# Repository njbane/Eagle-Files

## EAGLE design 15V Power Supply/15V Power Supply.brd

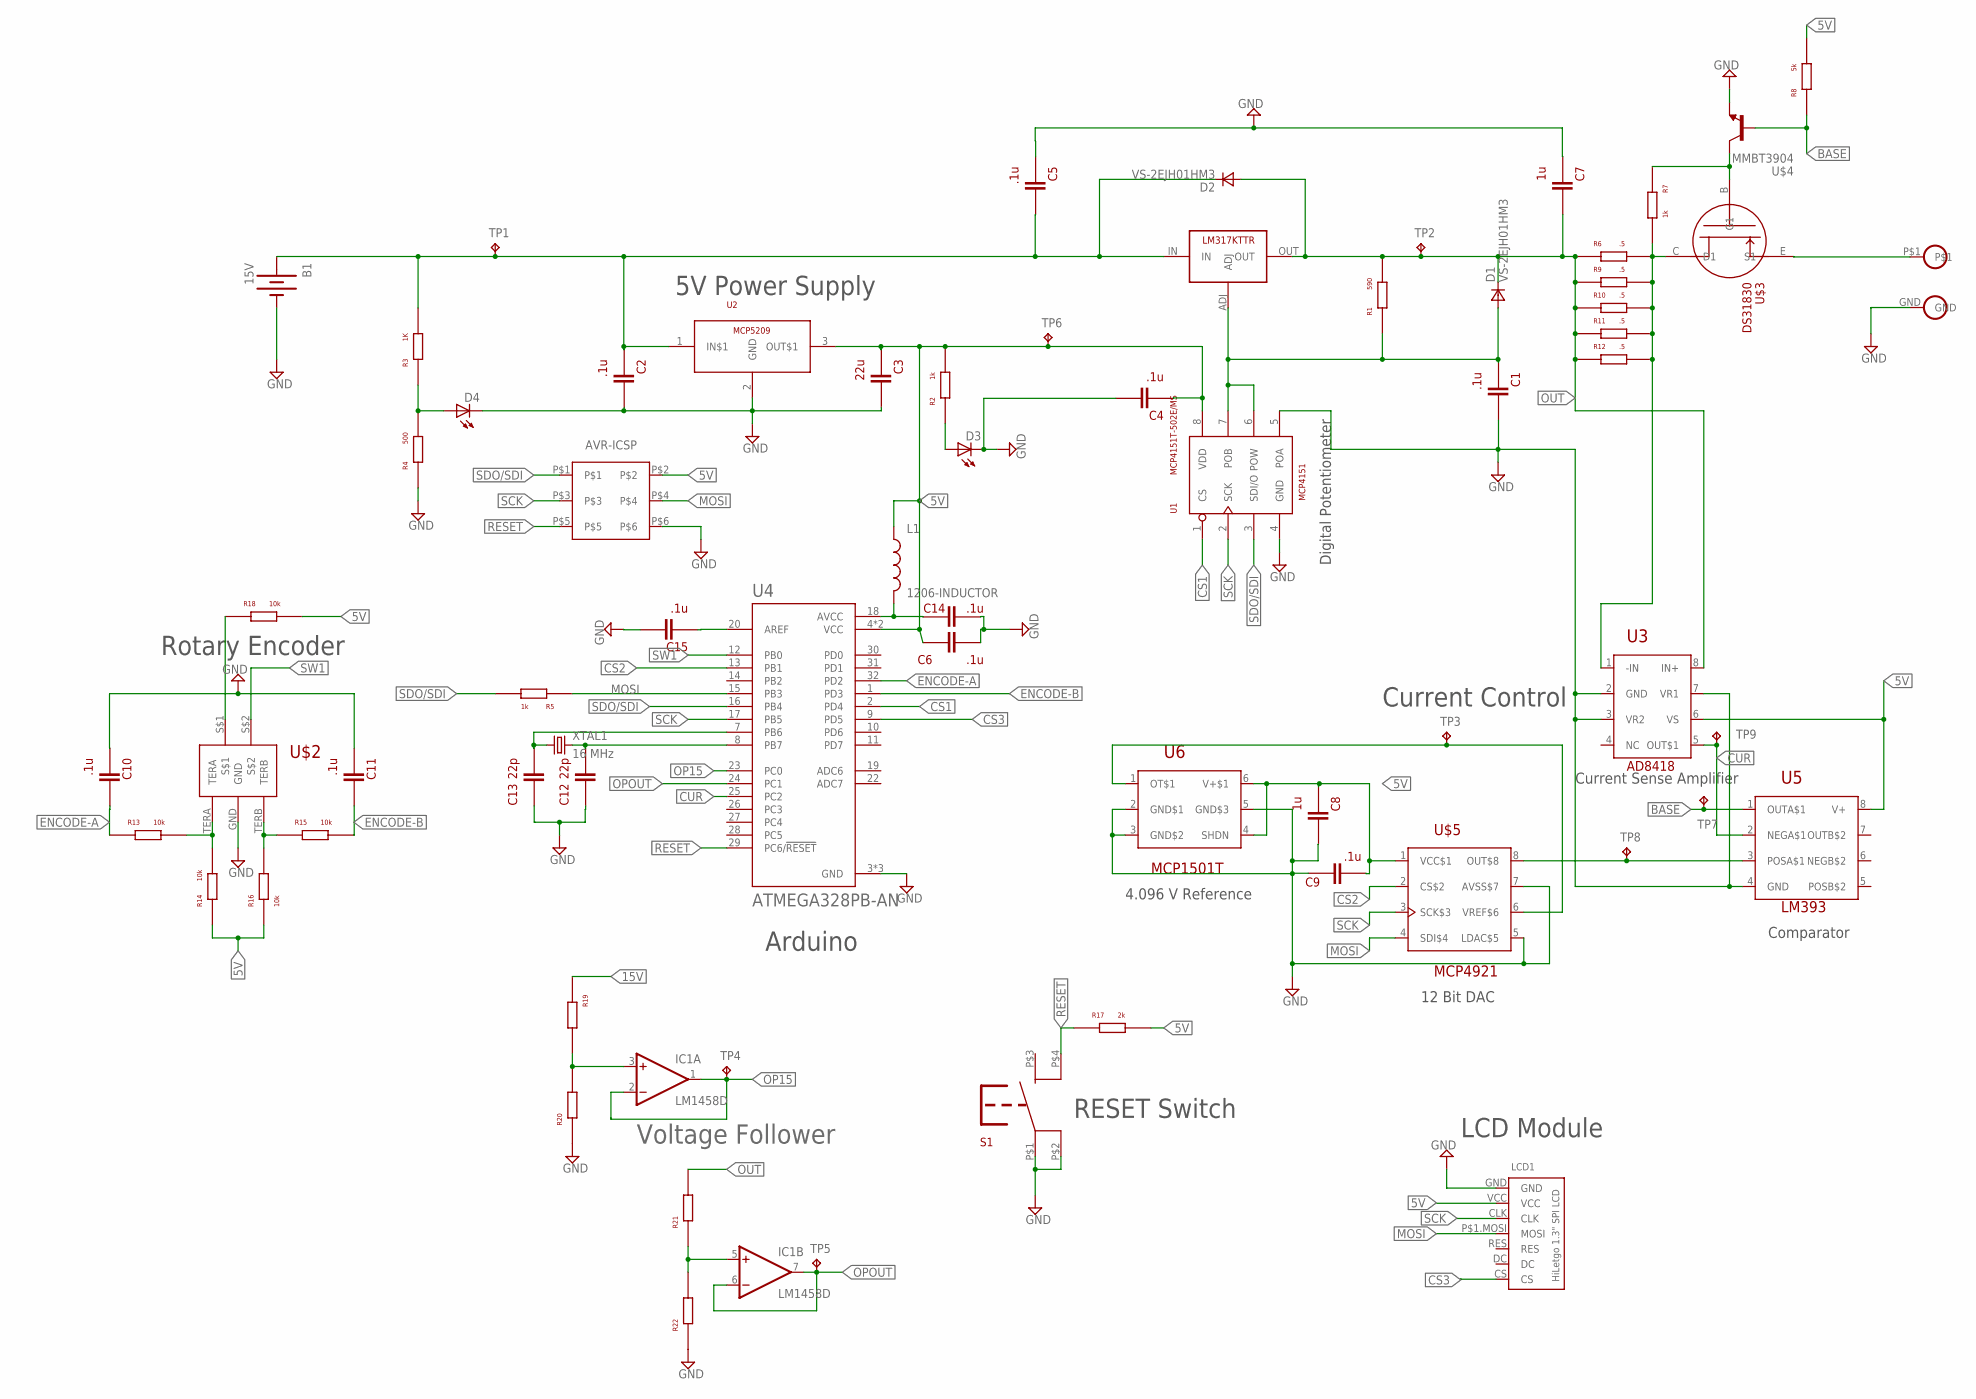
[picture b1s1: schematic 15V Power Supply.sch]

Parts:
B1: 15V; 2.1BARRELJACK
C1, C2, C4, C5, C6, C9, C10, C11, C14, C15: .1u; 1206CAP
C3: 22u; 1206CAP
C7, C8: 1u; 1206CAP
C12, C13: 22p; 1206CAP
D1, D2: VS-2EJH01HM3; DO-221AC-2
D3, D4: 1206LEDDIODE; 1206
IC1: LM1458D; SO08
L1: 1206-INDUCTOR; 1206
LCD1: HILETGOSPILCD
R1: 590; 1206
R2, R5, R7: 1k; 1206
R3: 1K; 1206
R4: 500; 1206
R6, R9, R10, R11, R12: .5; 1206
R8: 5k; 1206
R13, R14, R15, R16, R18: 10k; 1206
R17: 2k; 1206
R19, R20, R21, R22: 1206RESISTOR; 1206
S1: TL3305
TP1, TP2, TP3, TP4, TP5, TP6: TPTP11R; TP11R
TP7: TPPAD1-13; P1-13
TP8, TP9: TPB1,27; B1,27
U1: MCP4151T-502E/MS; DGK_S-PDSO-G8
U2: MCP5209-5.0YS; SOT223
U3: AD8418BZR; DGK_S-PDSO-G8
U4: ATMEGA328PB-AN; QFP80P900X900X120-32N
U5: LM393; SO8
U6: MCP1501T-40E/CHY; SOT23-6
U$1: LM317KTTR
U$2: PEC11R; PEC11R-4
U$3: DS31830; SC59-EBC
U$4: MMBT3904; SC59-EBC
U$5: MCP4921-E/SN; SO8
U$6: ICSP-HEADER; ISCP-PORT
U$7: BINDINGPOST; CT2232
XTAL1: 16 MHz; HC/49US

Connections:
5V: C3.P$2, C4.P$2, C6.P$1, C8.P$2, C9.P$1, IC1.8 (V+), L1.P$1 (1), LCD1.VCC, R2.P$1, R8.P$1, R14.P$2, R16.P$2, R17.P$1, R18.P$1, TP6.TP, U1.8 (VDD), U2.3 (OUT$1), U3.6 (VS), U4.4 (VCC), U4.6 (VCC), U5.8 (V+), U6.4 (SHDN), U6.6 (V+$1), U$5.1 (VCC$1), U$6.P$2
15V: B1.POS, C2.P$2, C5.P$1, D2.C$1 (C), R3.P$1, R19.P$2, TP1.TP, U2.1 (IN$1), U$1.IN
BASE: R8.P$2, TP7.TP, U5.1 (OUTA$1), U$4.B
CS1: U1.1 (CS), U4.2 (PD4)
CS2: U4.13 (PB1), U$5.2 (CS$2)
CS3: LCD1.CS, U4.9 (PD5)
CUR: TP9.TP, U3.5 (OUT$1), U4.25 (PC2), U5.2 (NEGA$1)
ENCODE-A: C10.P$1, R13.P$2, U4.32 (PD2)
ENCODE-B: C11.P$1, R15.P$1, U4.1 (PD3)
GND: B1.GND$1 (GND), C1.P$1, C2.P$1, C3.P$1, C4.P$1, C5.P$2, C6.P$2, C7.P$2, C8.P$1, C9.P$2, C10.P$2, C11.P$2, C12.P$1, C13.P$1, C14.P$2, C15.P$1, D3.P$2 (C), D4.P$2 (C), IC1.4 (V-), LCD1.GND, R4.P$2, R20.P$2, R22.P$2, S1.P$1, S1.P$2, U1.4 (GND), U1.5 (POA), U2.2 (GND), U3.2 (GND), U3.3 (VR2), U3.7 (VR1), U4.3 (GND), U4.5 (GND), U4.21 (GND), U5.4 (GND), U6.2 (GND$1), U6.3 (GND$2), U6.5 (GND$3), U$2.GND, U$4.E, U$5.5 (LDAC$5), U$5.7 (AVSS$7), U$6.P$6, U$7.GND
MOSI: LCD1.P$1.MOSI (MOSI), R5.P$2, U4.15 (PB3), U$5.4 (SDI$4), U$6.P$4
unnamed: D4.P$1 (A), R3.P$2, R4.P$1
unnamed: U$3.E (S1), U$7.P$1
unnamed: C1.P$2, D1.A$1 (A), R1.P$2, U1.6 (POW), U1.7 (POB), U$1.ADJ
unnamed: TP3.TP, U6.1 (OT$1), U$5.6 (VREF$6)
unnamed: D3.P$1 (A), R2.P$2
unnamed: C14.P$1, L1.P$2 (2), U4.18 (AVCC)
unnamed: C13.P$2, U4.7 (PB6), XTAL1.P$1 (1)
unnamed: TP8.TP, U5.3 (POSA$1), U$5.8 (OUT$8)
unnamed: R6.P$1, R7.P$1, R9.P$1, R10.P$1, R11.P$1, R12.P$1, U3.1 (-IN), U$3.C (D1)
unnamed: R13.P$1, R14.P$1, U$2.TERA
unnamed: R15.P$2, R16.P$1, U$2.TERB
unnamed: C12.P$2, U4.8 (PB7), XTAL1.P$2 (2)
unnamed: R7.P$2, U$3.B (G1), U$4.C
unnamed: C15.P$2, U4.20 (AREF)
unnamed: R18.P$2, U$2.S$1
unnamed: IC1.3 (+IN), R19.P$1, R20.P$1
unnamed: IC1.5 (+IN), R21.P$2, R22.P$1
OP15: IC1.1 (OUT), IC1.2 (-IN), TP4.TP, U4.23 (PC0)
OPOUT: IC1.6 (-IN), IC1.7 (OUT), TP5.TP, U4.24 (PC1)
OUT: C7.P$1, D1.C$1 (C), D2.A$1 (A), R1.P$1, R6.P$2, R9.P$2, R10.P$2, R11.P$2, R12.P$2, R21.P$1, TP2.TP, U3.8 (IN+), U$1.OUT
RESET: R17.P$2, S1.P$4, U4.29 (PC6/!RESET), U$6.P$5
SCK: LCD1.CLK, U1.2 (SCK), U4.17 (PB5), U$5.3 (SCK$3), U$6.P$3
SDO/SDI: R5.P$1, U1.3 (SDI/O), U4.16 (PB4), U$6.P$1
SW1: U4.12 (PB0), U$2.S$2

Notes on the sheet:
Current Control
Rotary Encoder
Arduino
5V Power Supply
4.096 V Reference
12 Bit DAC
Current Sense Amplifier
Comparator
Digital Potentiometer
RESET Switch
Voltage Follower
LCD Module

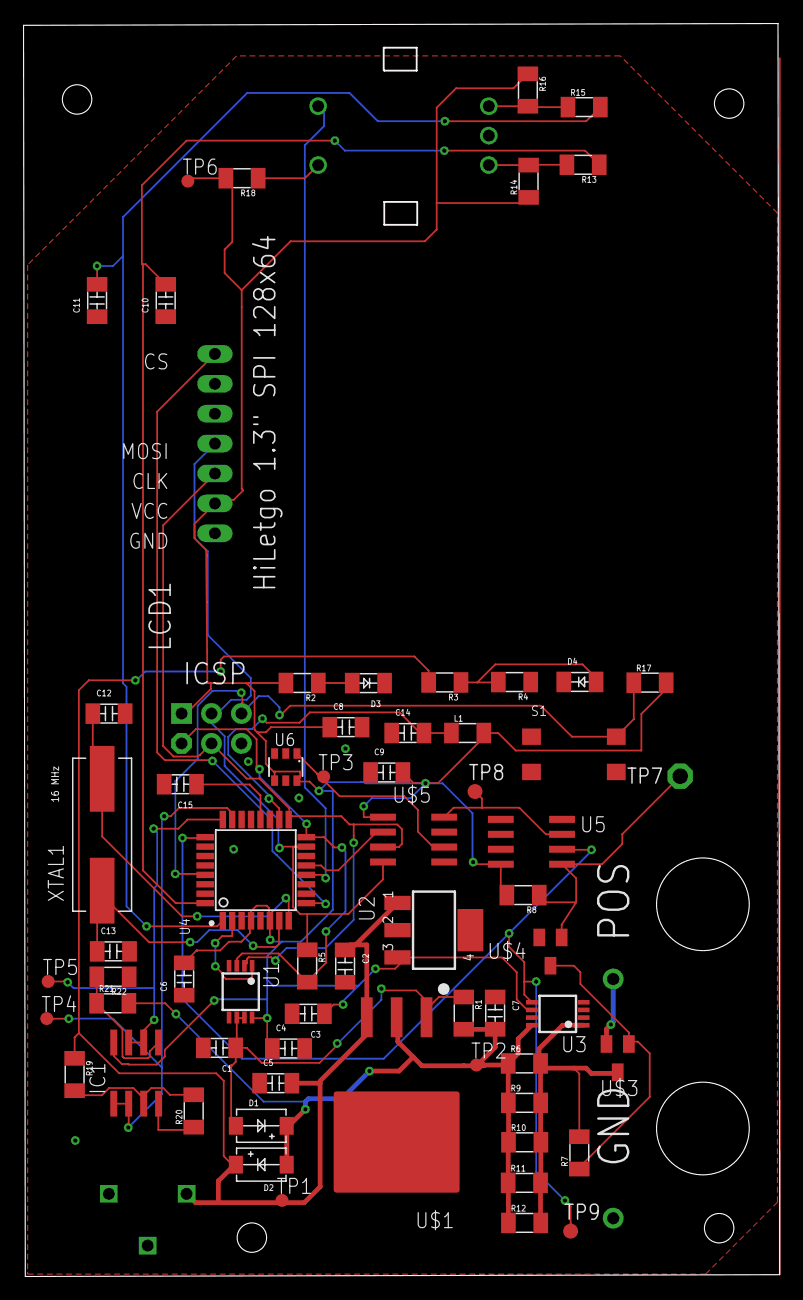
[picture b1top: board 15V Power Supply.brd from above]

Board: 2 copper layers, 64.2 x 106.5 mm, 69 parts (0 on the bottom side), 35 nets.

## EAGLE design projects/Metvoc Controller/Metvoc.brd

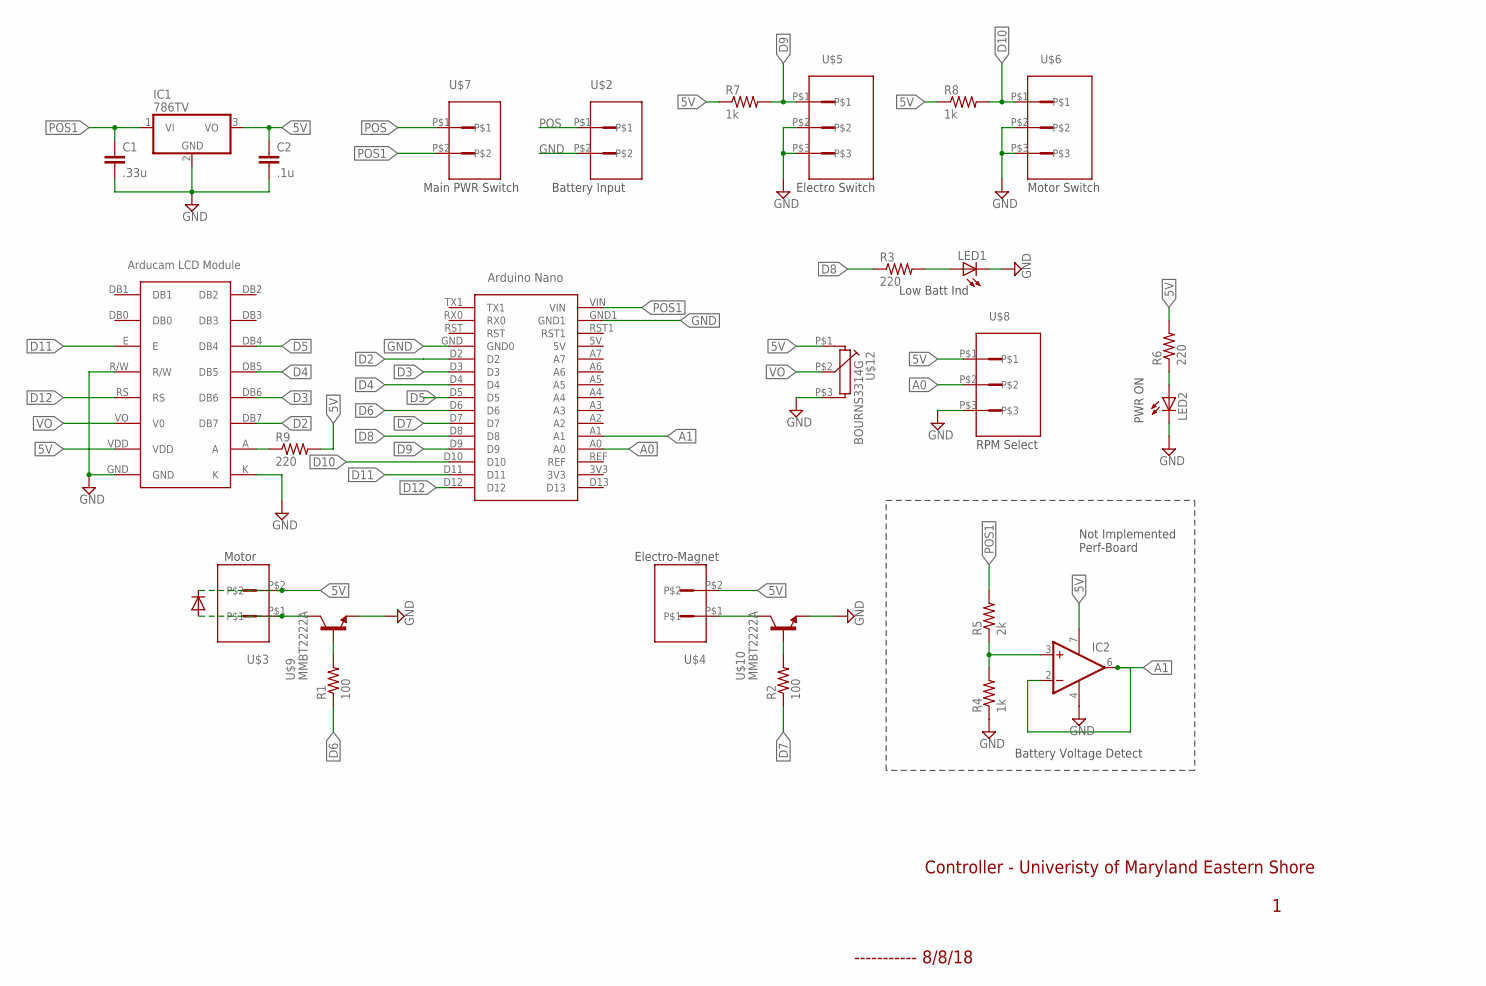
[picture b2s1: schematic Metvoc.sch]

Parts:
C1: .33u; C3216
C2: .1u; C3216
IC1: 786TV; TO220V
IC2: 1AMP_P7+4D; SO08
LED1, LED2: LED_E; LED_1206
R1, R2: 100; M1206
R3, R9: 220; M1206
R4, R7, R8: 1k; M1206
R5: 2k; M1206
R6: 220; M3216
U$1: ARDUINO_NANO; ARDUINONANO
U$2, U$3, U$4, U$7: KF2510-2; KF2540-2
U$5, U$6, U$8: KF2510-3; KF2540-3
U$9, U$10: MMBT2222A; SOT23
U$11: LCDMODULE; LCDSCREEN
U$12: BOURNS3314G; 3314POT

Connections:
5V: C2.1, IC1.3 (VO), IC2.7 (V+), R6.2, R7.1, R8.1, R9.2, U$3.P$2, U$4.P$2, U$8.P$1, U$11.VDD, U$12.P$1 (1A)
A0: U$1.A0, U$8.P$2
A1: IC2.2 (-IN), IC2.6 (OUT), U$1.A1
D2: U$1.D2, U$11.DB7
D3: U$1.D3, U$11.DB6
D4: U$1.D4, U$11.DB5
D5: U$1.D5, U$11.DB4
D6: R1.1, U$1.D6
D7: R2.1, U$1.D7
D8: R3.1, U$1.D8
D9: R7.2, U$1.D9, U$5.P$1
D10: R8.2, U$1.D10, U$6.P$1
D11: U$1.D11, U$11.E
D12: U$1.D12, U$11.RS
GND: C1.2, C2.2, IC1.2 (GND), IC2.4 (V-), LED1.C, LED2.C, R4.1, U$1.GND (GND0), U$1.GND1, U$2.P$2, U$5.P$2, U$5.P$3, U$6.P$2, U$6.P$3, U$8.P$3, U$9.2 (E), U$10.2 (E), U$11.GND, U$11.K, U$11.R/W, U$12.P$3 (1E)
unnamed: R1.2, U$9.1 (B)
unnamed: U$3.P$1, U$9.3 (C)
unnamed: U$4.P$1, U$10.3 (C)
unnamed: IC2.3 (+IN), R4.2, R5.1
unnamed: R2.2, U$10.1 (B)
unnamed: LED1.A, R3.2
unnamed: LED2.A, R6.1
unnamed: R9.1, U$11.A
POS: U$2.P$1, U$7.P$1
POS1: C1.1, IC1.1 (VI), R5.2, U$1.VIN, U$7.P$2
VO: U$11.VO (V0), U$12.P$2 (1S)

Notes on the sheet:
Battery Input
Motor
Electro-Magnet
RPM Select
Main PWR Switch
Low Batt Ind
Electro Switch
Motor Switch
PWR ON
Not Implemented Perf-Board
Battery Voltage Detect
Controller - Univeristy of Maryland Eastern Shore
----------- 8/8/18

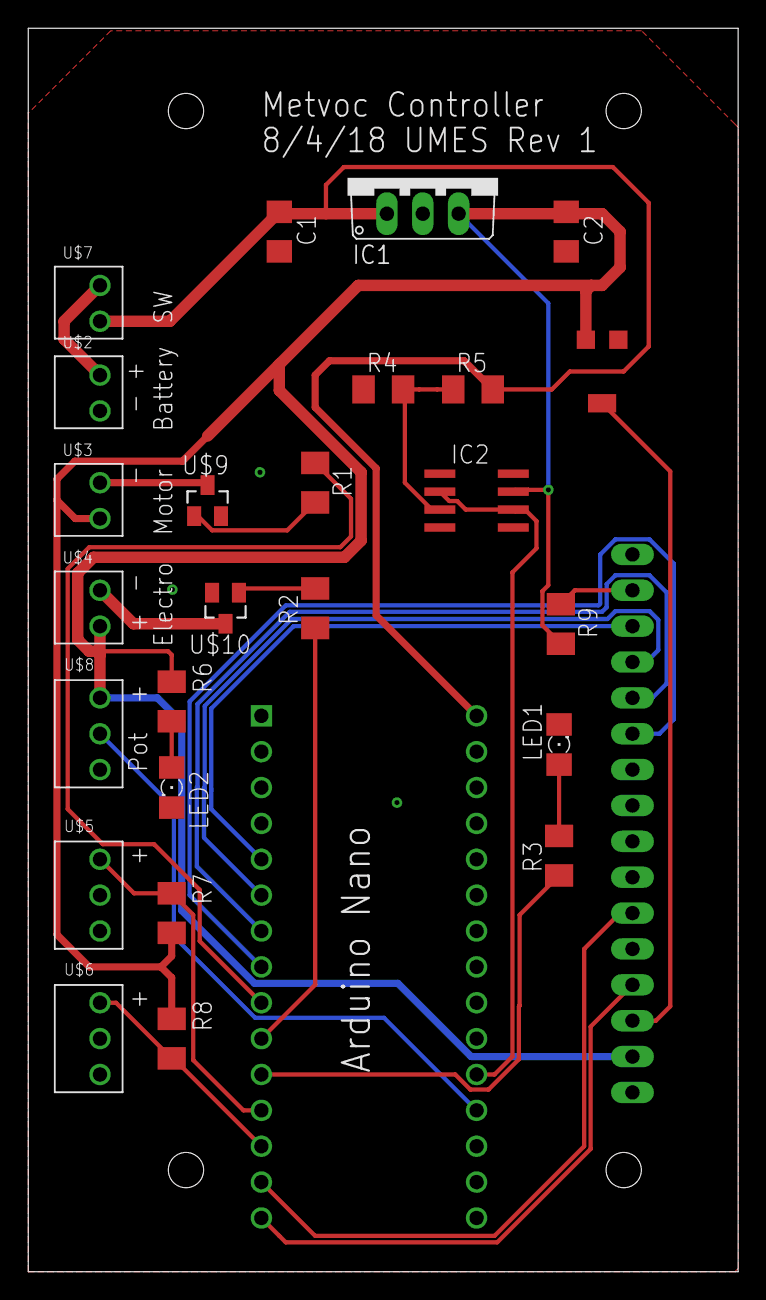
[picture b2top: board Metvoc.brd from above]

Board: 2 copper layers, 50.3 x 88.1 mm, 27 parts (1 on the bottom side), 26 nets.

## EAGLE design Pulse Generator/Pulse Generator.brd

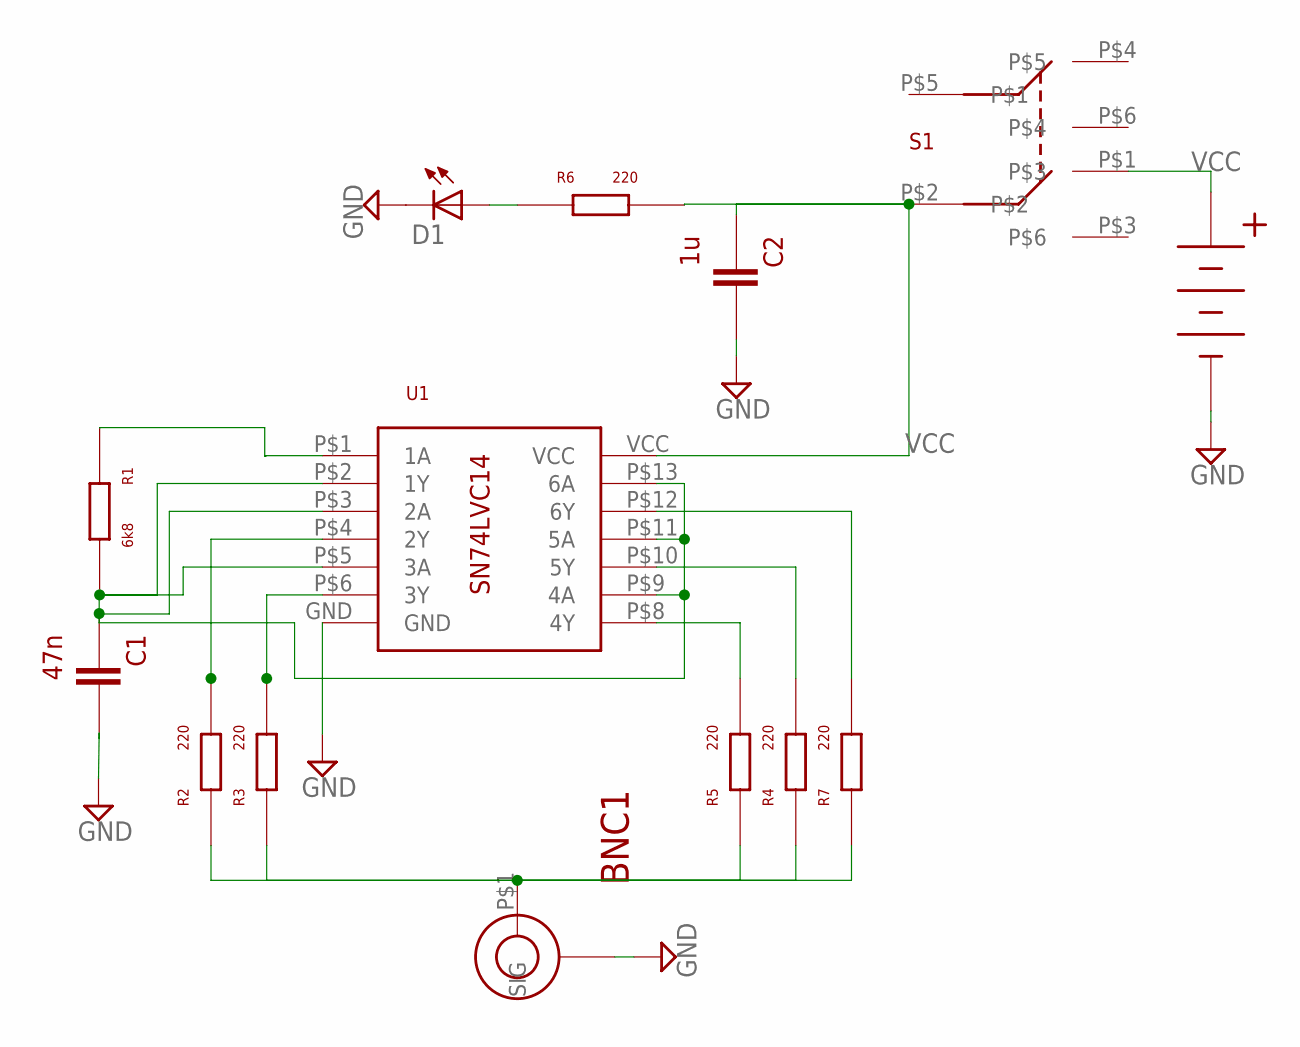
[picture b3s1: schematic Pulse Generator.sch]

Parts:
BNC1: TE-1-337543; PCBBNC
C1: 47n; 1206CAP
C2: 1u; 1206CAP
D1: 1206LEDDIODE; 1206
R1: 6k8; 1206
R2, R3, R4, R5, R6, R7: 220; 1206
S1: JS202011SCQN
U1: SN74LVC14A; SOIC-14
U$1: 1042-18650BATTERYHOLE; BATTHRHOLE

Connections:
GND: BNC1.P$2 (GND), C1.P$1, C2.P$1, D1.P$2 (C), U1.GND, U$1.GND
unnamed: R3.P$1, U1.P$6 (3Y)
unnamed: R2.P$1, U1.P$4 (2Y)
unnamed: R5.P$1, U1.P$8 (4Y)
unnamed: R4.P$1, U1.P$10 (5Y)
unnamed: R7.P$1, U1.P$12 (6Y)
unnamed: BNC1.P$1 (SIG), R2.P$2, R3.P$2, R4.P$2, R5.P$2, R7.P$2
unnamed: C1.P$2, R1.P$1, U1.P$2 (1Y), U1.P$3 (2A), U1.P$5 (3A), U1.P$9 (4A), U1.P$11 (5A), U1.P$13 (6A)
unnamed: D1.P$1 (A), R6.P$2
unnamed: R1.P$2, U1.P$1 (1A)
VCC: C2.P$2, R6.P$1, S1.P$1, S1.P$2, U1.VCC, U$1.VCC

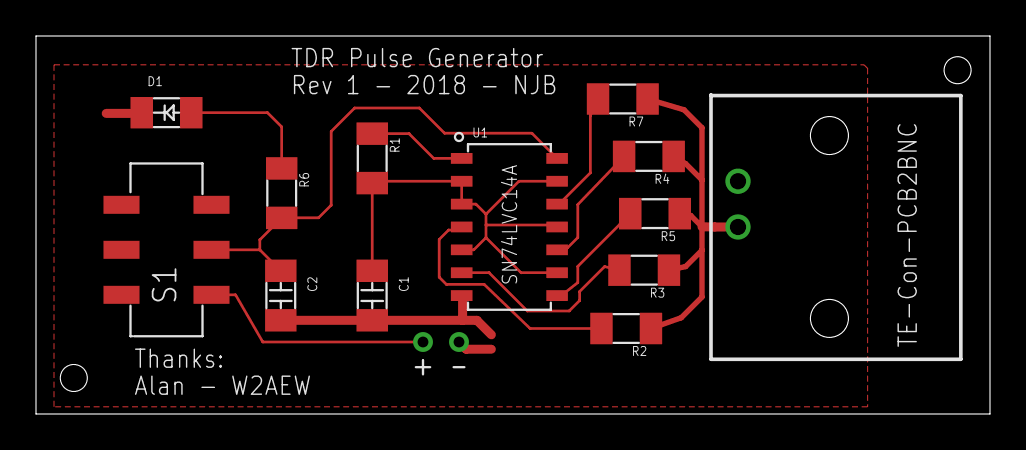
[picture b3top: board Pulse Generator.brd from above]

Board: 2 copper layers, 53.0 x 21.0 mm, 14 parts (0 on the bottom side), 11 nets.

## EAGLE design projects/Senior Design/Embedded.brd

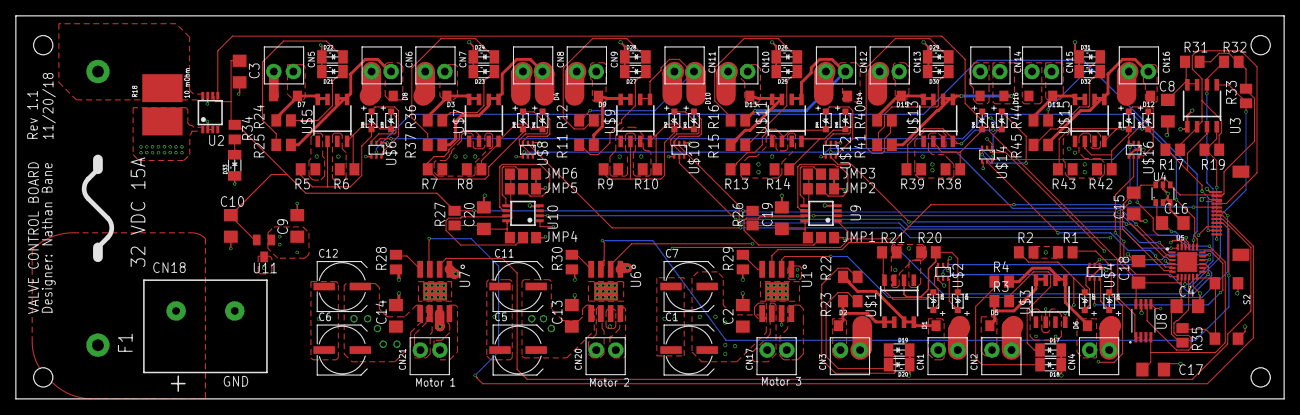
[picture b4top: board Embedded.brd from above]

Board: 4 copper layers, 164.8 x 49.8 mm, 170 parts (0 on the bottom side), 118 nets.

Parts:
C1, C5, C6, C7, C11, C12: 47uF; UD-6,3X7,7_NICHICON
C2, C3, C4, C8, C13, C14, C15, C17, C18, C19, C20: 1uF; C1206
C9: 1 uF; C1206
C10: .5 uF; C1206
C16: .5uF; C1206
CN1, CN2, CN3, CN4, CN5, CN6, CN7, CN8, CN9, CN10, CN11, CN12, CN13, CN14, CN15, CN16, CN17, CN20, CN21: KF2510-2; KF2540-2
CN18: PHEON_MKDS_CON; PHOEN_MKDS
CN19: MOLEX_FPC_52892_1233; MOLEX_WM1108
D1, D2, D3, D4, D5, D6, D7, D8, D9, D10, D11, D12, D13, D14, D15, D16: RS1AL_DIODE; DO219
D17, D18, D19, D20, D21, D22, D23, D24, D25, D26, D27, D28, D29, D30, D31, D32, D33: 1206LED; 1206
D34, D35, D37, D38, D39, D40, D41, D42, D43, D44, D45, D46, D47, D48, D49: 6.2V; SOD_323F
D36: 6.2; SOD_323F
F1: 32 VDC 15A; LITTLEFUSE125_003
JMP1, JMP2, JMP3, JMP4, JMP5, JMP6: 0R-JUMPA; A0R-JMP
R1, R2, R3, R4, R5, R7, R8, R9, R10, R11, R12, R13, R14, R15, R16, R20, R21, R22, R23, R24, R25, R36, R37, R38, R39, R40, R41, R42, R43, R44, R45: 5k; M0805
R6: 1k; M0805
R17, R19, R32, R33, R35: 10k; M0805
R18: 10 mOhm; 2818
R26, R27, R34: 200; M0805
R28, R29, R30: 18k; M0805
R31: 200k; M0805
S2: TL3305
U1, U6, U7: DRV8871; SO8_EP
U2: AD8418BZR; DGK_S-PDSO-G8
U3: GTL2002; SO-8
U4: MCP1501T-40E/CHY; SOT23-6
U5: MCP23018; QFN_24_EP
U8: MAX11645UMAX8; UMAX8
U9, U10: TCN75A; DGK_S-PDSO-G8
U11: RT9058-50GV; SOT23
U$1, U$3, U$5, U$7, U$9, U$11, U$13, U$15: IRF9953PBF; SO-8
U$2, U$4, U$6, U$8, U$10, U$12, U$14, U$16: UM6K31N; UMT6

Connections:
3.3V: CN19.P$9, R17.2, R19.2, U3.2
4.096V: C16.1, C17.1, U4.1, U8.P$4
5V: C3.1, C4.1, C10.1, C15.1, C18.1, CN19.P$11, R26.2, R27.2, R31.2, R32.2, R33.2, R34.2, R35.2, U2.6, U4.4, U4.6, U5.P8, U8.P$8, U11.2
12V_OUT: C1.+, C2.1, C5.+, C6.+, C7.+, C9.1, C11.+, C12.+, C13.1, C14.1, CN19.P$10, R1.2, R2.2, R5.2, R6.2, R7.2, R8.2, R9.2, R10.2, R13.2, R14.2, R18.P$1, R20.2, R21.2, R38.2, R39.2, R42.2, R43.2, U1.P5, U2.1, U6.P5, U7.P5, U11.1, U$1.1, U$1.3, U$3.1, U$3.3, U$5.1, U$5.3, U$7.1, U$7.3, U$9.1, U$9.3, U$11.1, U$11.3, U$13.1, U$13.3, U$15.1, U$15.3
+12V: F1.P$1, R18.P$2, U2.8
BD1: CN19.P$3, U6.P2
BD2: CN19.P$4, U6.P3
BD3: CN19.P$5, U7.P2
BD4: CN19.P$6, U7.P3
BD5: CN19.P$7, U1.P2
BD6: CN19.P$8, U1.P3
GND: C1.-, C2.2, C3.2, C4.2, C5.-, C6.-, C7.-, C8.2, C9.2, C10.2, C11.-, C12.-, C13.2, C14.2, C15.2, C16.2, C17.2, C18.2, C19.2, C20.2, CN1.P$2, CN2.P$2, CN3.P$2, CN4.P$2, CN5.P$2, CN6.P$2, CN7.P$2, CN8.P$2, CN9.P$2, CN10.P$2, CN11.P$2, CN12.P$2, CN13.P$2, CN14.P$2, CN15.P$2, CN16.P$2, CN18.P$2, CN19.P$12, D1.A$2, D2.A$2, D3.A$2, D4.A$2, D5.A$2, D6.A$2, D7.A$2, D8.A$2, D9.A$2, D10.A$2, D11.A$2, D12.A$2, D13.A$2, D14.A$2, D15.A$2, D16.A$2, D17.P$2, D18.P$2, D19.P$2, D20.P$2, D21.P$2, D22.P$2, D23.P$2, D24.P$2, D25.P$2, D26.P$2, D27.P$2, D28.P$2, D29.P$2, D30.P$2, D31.P$2, D32.P$2, D33.P$2, JMP1.1, JMP2.1, JMP3.1, JMP4.1, JMP5.1, JMP6.1, R28.1, R29.1, R30.1, S2.P$1, S2.P$2, U1.GND, U1.P1, U1.P7, U1.P$1, U1.P$2, U1.P$3, U1.P$4, U1.P$5, U1.P$6, U1.P$7, U1.P$8, U1.P$9, U1.P$10, U1.P$11, U1.P$12, U2.2, U2.3, U2.7, U3.1, U4.2, U4.3, U4.5, U5.P11, U5.P23, U6.GND, U6.P1, U6.P7, U6.P$1, U6.P$2, U6.P$3, U6.P$4, U6.P$5, U6.P$6, U6.P$7, U6.P$8, U6.P$9, U6.P$10, U6.P$11, U6.P$12, U7.GND, U7.P1, U7.P7, U7.P$1, U7.P$2, U7.P$3, U7.P$4, U7.P$5, U7.P$6, U7.P$7, U7.P$8, U7.P$9, U7.P$10, U7.P$11, U7.P$12, U8.P$7, U9.4, U10.4, U11.3, U$2.1, U$2.4, U$4.1, U$4.4, U$6.1, U$6.4, U$8.1, U$8.4, U$10.1, U$10.4, U$12.1, U$12.4, U$14.1, U$14.4, U$16.1, U$16.4
IOUT: U2.5, U8.P$1, U8.P$2
KLJL: C8.1, R31.1, U3.7, U3.8
MC1: U5.P15, U$2.2
MC2: U5.P16, U$2.5
MC3: U5.P17, U$4.2
MC4: U5.P18, U$4.5
MC5: U5.P19, U$6.2
MC6: U5.P20, U$6.5
MC7: U5.P21, U$8.2
MC8: U5.P22, U$8.5
MC9: U5.P24, U$10.2
MC10: U5.P1, U$10.5
MC11: U5.P2, U$12.2
MC12: U5.P3, U$12.5
MC13: U5.P4, U$14.2
MC14: U5.P5, U$14.5
MC15: U5.P6, U$16.2
MC16: U5.P7, U$16.5
unnamed: D35.C, R21.1, U$1.4
unnamed: D35.A, U$2.3
unnamed: R29.2, U1.P4
unnamed: D37.C, R2.1, U$3.4
unnamed: D39.A, U$6.3
unnamed: D39.C, R6.1, U$5.4
unnamed: D40.A, U$8.6
unnamed: D41.C, R8.1, U$7.4
unnamed: D43.C, R10.1, U$9.4
unnamed: D45.C, R14.1, U$11.4
unnamed: D47.C, R39.1, U$13.4
unnamed: D49.C, R43.1, U$15.4
unnamed: D44.C, R13.1, U$11.2
unnamed: D45.A, U$12.3
unnamed: D43.A, U$10.3
unnamed: D42.C, R9.1, U$9.2
unnamed: D36.C, R1.1, U$3.2
unnamed: CN17.P$2, U1.P8
unnamed: D37.A, U$4.3
unnamed: D33.P$1, R34.1
unnamed: CN17.P$1, U1.P6
unnamed: JMP1.2, U9.7
unnamed: JMP2.2, U9.6
unnamed: JMP3.2, U9.5
unnamed: JMP4.2, U10.7
unnamed: JMP5.2, U10.6
unnamed: D36.A, U$4.6
unnamed: D34.C, R20.1, U$1.2
unnamed: D34.A, U$2.6
unnamed: D47.A, U$14.3
unnamed: D46.C, R38.1, U$13.2
unnamed: D49.A, U$16.3
unnamed: D48.C, R42.1, U$15.2
unnamed: D42.A, U$10.6
unnamed: D27.P$1, R11.2
unnamed: D38.A, U$6.6
unnamed: D38.C, R5.1, U$5.2
unnamed: D40.C, R7.1, U$7.2
unnamed: D41.A, U$8.3
unnamed: D28.P$1, R12.1
unnamed: D44.A, U$12.6
unnamed: R30.2, U6.P4
unnamed: R28.2, U7.P4
unnamed: CN20.P$2, U6.P8
unnamed: CN20.P$1, U6.P6
unnamed: CN21.P$1, U7.P6
unnamed: CN21.P$2, U7.P8
unnamed: JMP6.2, U10.5
unnamed: D19.P$1, R22.2
unnamed: D20.P$1, R23.1
unnamed: D17.P$1, R3.2
unnamed: D18.P$1, R4.1
unnamed: D22.P$1, R25.1
unnamed: D21.P$1, R24.2
unnamed: D24.P$1, R37.1
unnamed: D23.P$1, R36.2
unnamed: D25.P$1, R15.2
unnamed: D26.P$1, R16.1
unnamed: D46.A, U$14.6
unnamed: D30.P$1, R41.1
unnamed: D29.P$1, R40.2
unnamed: D48.A, U$16.6
unnamed: D32.P$1, R45.1
unnamed: D31.P$1, R44.2
unnamed: CN18.P$1, F1.P$2
ONKL: C20.1, JMP4.3, JMP5.3, JMP6.3, R27.1, U10.8
RESET: R35.1, S2.P$3, S2.P$4, U5.P12
SCL3.3: CN19.P$2, R17.1, U3.3
SCL5: R32.1, U3.6, U5.P9, U8.P$5, U9.2, U10.2
SDA3.3: CN19.P$1, R19.1, U3.4
SDA5: R33.1, U3.5, U5.P10, U8.P$6, U9.1, U10.1
UOY: C19.1, JMP1.3, JMP2.3, JMP3.3, R26.1, U9.8
VAL_1: CN1.P$1, D1.C$1, R22.1, U$1.7, U$1.8
VAL_2: CN3.P$1, D2.C$1, R23.2, U$1.5, U$1.6
VAL_3: CN2.P$1, D5.C$1, R3.1, U$3.7, U$3.8
VAL_4: CN4.P$1, D6.C$1, R4.2, U$3.5, U$3.6
VAL_5: CN5.P$1, D7.C$1, R24.1, U$5.7, U$5.8
VAL_6: CN6.P$1, D8.C$1, R25.2, U$5.5, U$5.6
VAL_7: CN7.P$1, D3.C$1, R36.1, U$7.7, U$7.8
VAL_8: CN8.P$1, D4.C$1, R37.2, U$7.5, U$7.6
VAL_9: CN9.P$1, D9.C$1, R11.1, U$9.7, U$9.8
VAL_10: CN11.P$1, D10.C$1, R12.2, U$9.5, U$9.6
VAL_11: CN10.P$1, D13.C$1, R15.1, U$11.7, U$11.8
VAL_12: CN12.P$1, D14.C$1, R16.2, U$11.5, U$11.6
VAL_13: CN13.P$1, D15.C$1, R40.1, U$13.7, U$13.8
VAL_14: CN14.P$1, D16.C$1, R41.2, U$13.5, U$13.6
VAL_15: CN15.P$1, D11.C$1, R44.1, U$15.7, U$15.8
VAL_16: CN16.P$1, D12.C$1, R45.2, U$15.5, U$15.6

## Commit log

2018-12-01 My Orginal Eagle Files
